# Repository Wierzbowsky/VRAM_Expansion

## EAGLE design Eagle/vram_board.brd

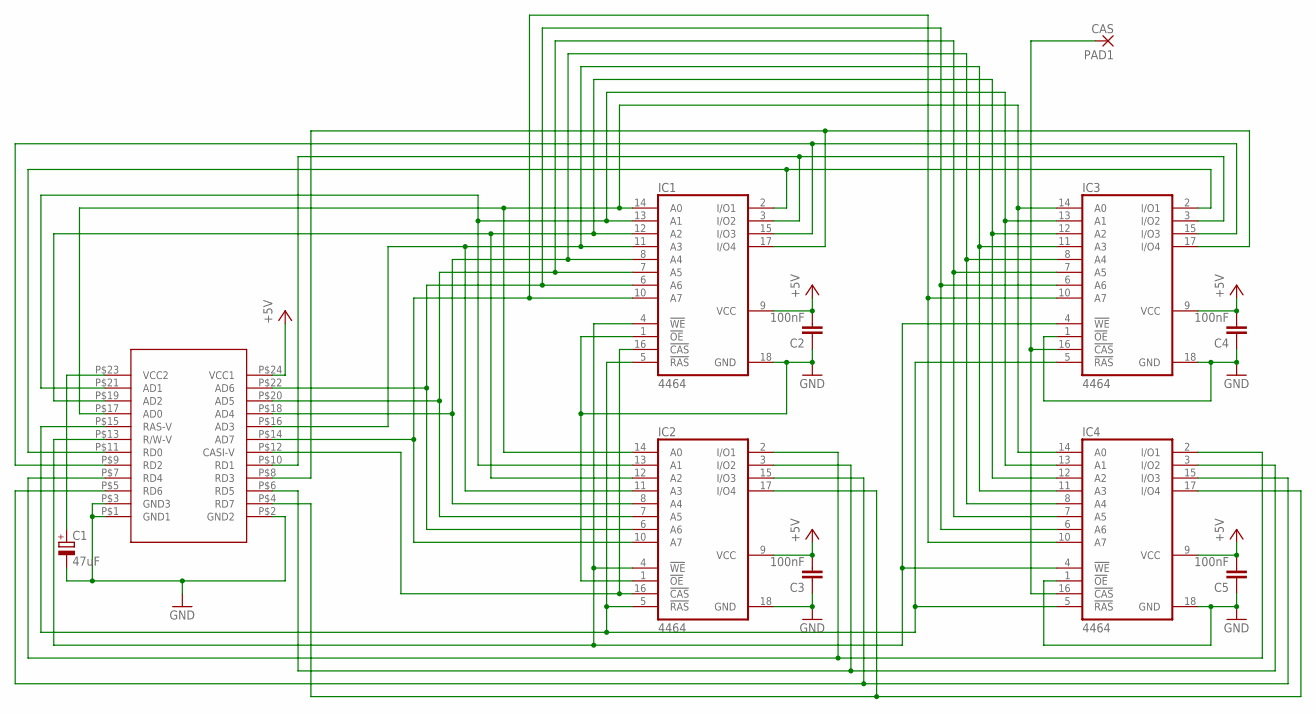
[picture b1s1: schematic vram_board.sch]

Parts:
C1: 47uF; E2-5
C2, C3, C4, C5: 100nF; C050-025X075
IC1, IC2, IC3, IC4: 4464; DIL18
PAD1: CAS; 1,6/0,9
U$1: CN24DR; VRAM_CONN

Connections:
GND: C1.-, C2.1, C3.1, C4.1, C5.1, IC1.1 (!OE), IC1.18 (GND), IC2.1 (!OE), IC2.18 (GND), IC3.1 (!OE), IC3.18 (GND), IC4.1 (!OE), IC4.18 (GND), U$1.P$1 (GND1), U$1.P$2 (GND2), U$1.P$3 (GND3)
unnamed: IC1.14 (A0), IC2.14 (A0), IC3.14 (A0), IC4.14 (A0), U$1.P$17 (AD0)
unnamed: IC1.12 (A2), IC2.12 (A2), IC3.12 (A2), IC4.12 (A2), U$1.P$19 (AD2)
unnamed: IC1.13 (A1), IC2.13 (A1), IC3.13 (A1), IC4.13 (A1), U$1.P$21 (AD1)
unnamed: IC1.11 (A3), IC2.11 (A3), IC3.11 (A3), IC4.11 (A3), U$1.P$16 (AD3)
unnamed: IC1.8 (A4), IC2.8 (A4), IC3.8 (A4), IC4.8 (A4), U$1.P$18 (AD4)
unnamed: IC1.7 (A5), IC2.7 (A5), IC3.7 (A5), IC4.7 (A5), U$1.P$20 (AD5)
unnamed: IC1.6 (A6), IC2.6 (A6), IC3.6 (A6), IC4.6 (A6), U$1.P$22 (AD6)
unnamed: IC1.10 (A7), IC2.10 (A7), IC3.10 (A7), IC4.10 (A7), U$1.P$14 (AD7)
unnamed: IC1.16 (!CAS), IC2.16 (!CAS), U$1.P$12 (CASI-V)
unnamed: IC1.5 (!RAS), IC2.5 (!RAS), IC3.5 (!RAS), IC4.5 (!RAS), U$1.P$15 (RAS-V)
unnamed: IC1.2 (I/O1), IC3.2 (I/O1), U$1.P$11 (RD0)
unnamed: IC1.4 (!WE), IC2.4 (!WE), IC3.4 (!WE), IC4.4 (!WE), U$1.P$13 (R/W-V)
unnamed: IC1.3 (I/O2), IC3.3 (I/O2), U$1.P$10 (RD1)
unnamed: IC1.15 (I/O3), IC3.15 (I/O3), U$1.P$9 (RD2)
unnamed: IC1.17 (I/O4), IC3.17 (I/O4), U$1.P$8 (RD3)
unnamed: IC2.2 (I/O1), IC4.2 (I/O1), U$1.P$7 (RD4)
unnamed: IC2.3 (I/O2), IC4.3 (I/O2), U$1.P$6 (RD5)
unnamed: IC2.15 (I/O3), IC4.15 (I/O3), U$1.P$5 (RD6)
unnamed: IC2.17 (I/O4), IC4.17 (I/O4), U$1.P$4 (RD7)
unnamed: IC3.16 (!CAS), IC4.16 (!CAS), PAD1.1
VCC: C2.2, C3.2, C4.2, C5.2, IC1.9 (VCC), IC2.9 (VCC), IC3.9 (VCC), IC4.9 (VCC), U$1.P$24 (VCC1)
VCC1: C1.+, U$1.P$23 (VCC2)

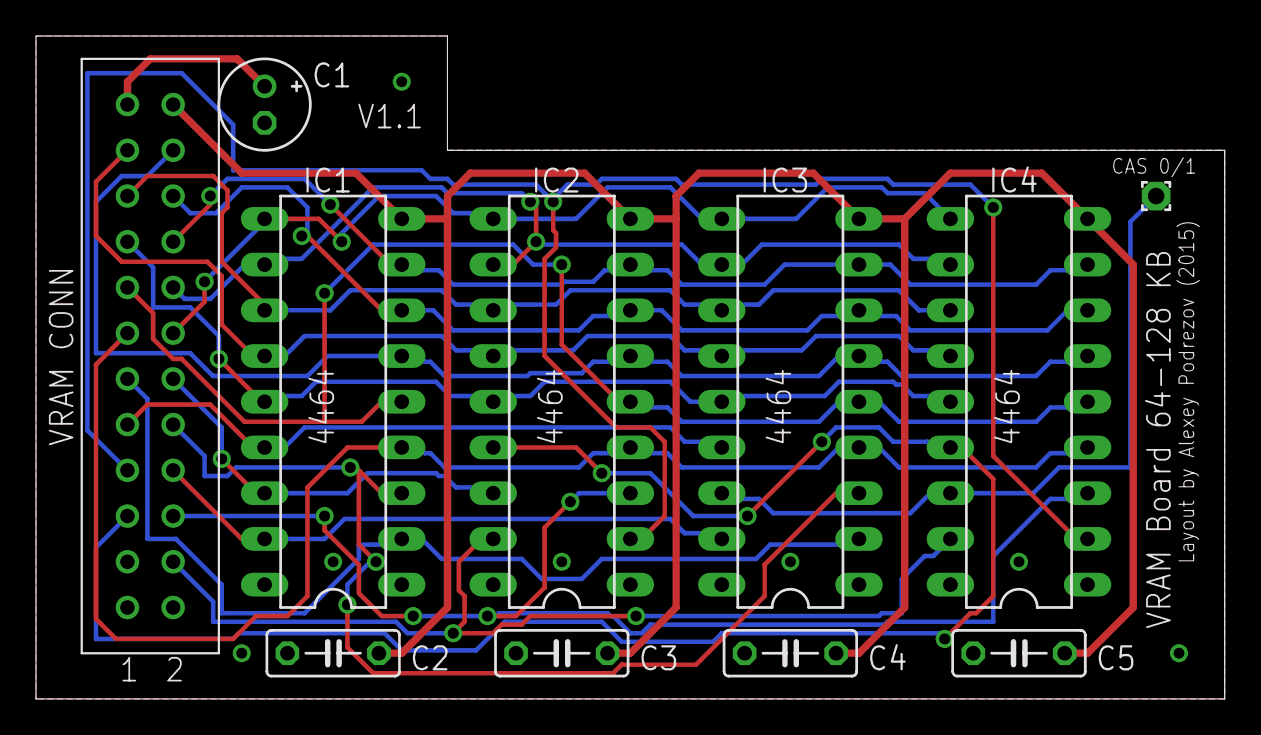
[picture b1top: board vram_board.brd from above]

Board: 2 copper layers, 66.0 x 36.8 mm, 11 parts (0 on the bottom side), 23 nets.

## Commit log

2015-12-30 :neckbeard: Added .gitattributes & .gitignore files
2015-12-30 VRAM Expansion for Yamaha MSX1
    VRAM Expansion for Yamaha MSX1 computers, expand by 64kb or 128kb
    (requires CAS wiring)
2016-05-27 Partslist
2017-05-20 Renamed board's folder
